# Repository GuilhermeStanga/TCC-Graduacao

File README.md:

# TCC-Graduacao
Trabalho de conclusão do curso Engenharia da Computação

	Mais detalhes no artigo em:
		https://siaiap32.univali.br/seer/index.php/acotb/article/view/12837
		
	Monografia:
		http://repositorio.roca.utfpr.edu.br/jspui/handle/1/8173
	
	Funcionamento no video:
		https://www.youtube.com/watch?v=rWx2oIafAY0&t=

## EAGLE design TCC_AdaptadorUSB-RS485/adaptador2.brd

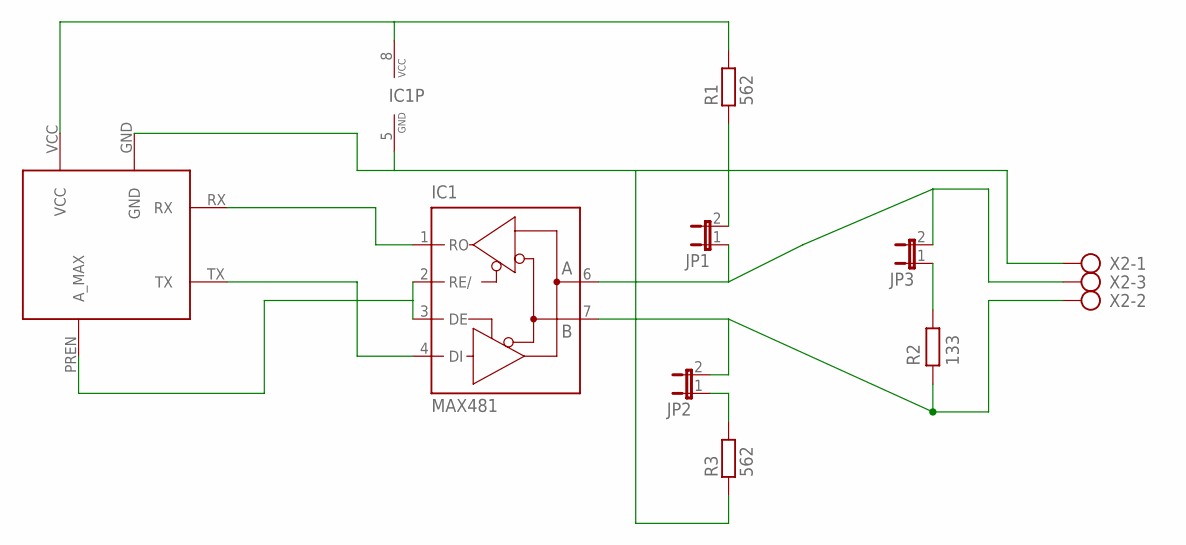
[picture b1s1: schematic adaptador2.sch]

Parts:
1: MOD_ADAPTADOR; ADAPTADOR
IC1: MAX481; DIL08
JP1, JP2, JP3: JP1E; JP1
R1, R3: 562; 0207/10
R2: 133; 0207/10
X2: AK300/3

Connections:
+5V_EXT: 1.VCC, IC1.8 (VCC), R1.2
GND_EXT: 1.GND, IC1.5 (GND), R3.1, X2.1
unnamed: JP1.2, R1.1
unnamed: JP2.1, R3.2
unnamed: JP3.1, R2.1
unnamed: 1.RX, IC1.1 (RO)
unnamed: 1.PREN (A_MAX), IC1.2 (RE/), IC1.3 (DE)
unnamed: 1.TX, IC1.4 (DI)
unnamed: IC1.7 (B), JP2.2, R2.2, X2.2
unnamed: IC1.6 (A), JP1.1, JP3.2, X2.3

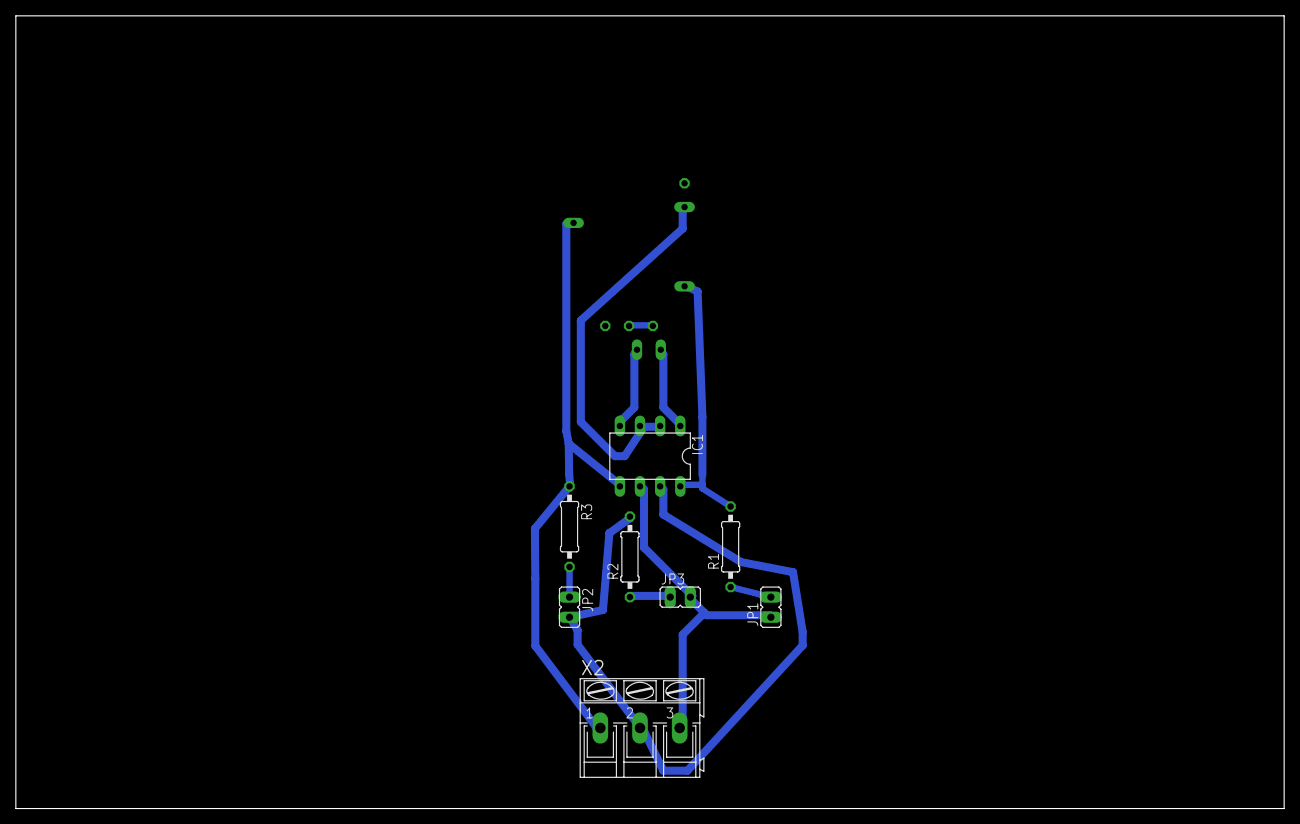
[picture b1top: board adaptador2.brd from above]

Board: 2 copper layers, 160.0 x 100.0 mm, 9 parts (1 on the bottom side), 10 nets.

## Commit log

2020-03-14 Commit Inicial
2020-03-14 adicionado link para documento
